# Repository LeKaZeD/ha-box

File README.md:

# HA Box

**HA Box** is an open-source, modular home automation hub built around a Raspberry Pi 5 and Home Assistant OS. It integrates the main smart home protocols (Zigbee, Thread, 433 MHz) into a single 3D-printed enclosure, with a custom ESP32 interface board providing a local E-Paper display, touch, environmental sensing, and physical controls.

---

## Project overview

HA Box is composed of four independent layers that work together:

```
+---------------------------------------------------------------+
|  3D-printed enclosure  (modular, FDM-printable, upgradeable)  |
|                                                               |
|  +---------------------------+   +-------------------------+  |
|  |  Raspberry Pi 5 stack     |   |  haboxesp PCB + ESP32   |  |
|  |  - Pi 5                   |   |  - E-Paper display      |  |
|  |  - M.2 SSD hat            |   |  - Touch (FT6336U)      |  |
|  |  - HDMI/USB-C extension   |   |  - BME280 sensor        |  |
|  |  - Sonoff Dongle Plus E   |   |  - Temp sensor TMP102   |  |
|  |    (Zigbee + Thread)      |   |  - Fan (PWM)            |  |
|  |  - CC1101 module (planned)|   |  - Buzzer               |  |
|  |    (433 MHz, SPI)         |   |  - Power button + J2    |  |
|  |                           |   |                         |  |
|  |  [ Home Assistant OS ]    |   |                         |  |
|  |  [ HA Box App (py) ]   <--+---+--> UART                 |  |
|  +---------------------------+   +-------------------------+  |
+---------------------------------------------------------------+
```

| Layer | Description | Location |
|-------|-------------|----------|
| **Hardware** | Pi 5 stack, haboxesp PCB, Sonoff dongle, connectors | `hardware/` |
| **3D enclosure** | Modular, printable enclosure for all components | `hardware/3D plan/` |
| **ESP32 firmware** | Drives display, sensors, touch, fan, buzzer | `ha-box-esp/` |
| **HA App** | Python app: UART bridge to HA API and Supervisor | `ha-box/` |
| **HA integration** | Custom component: groups all HA Box entities in the device registry | `ha-integration/` |

---

## Hardware

### Raspberry Pi 5 stack

| Component | Description | Protocol |
|-----------|-------------|----------|
| Raspberry Pi 5 | Main compute unit, runs Home Assistant OS | — |
| M.2 SSD hat | NVMe storage via PCIe | PCIe |
| HDMI + USB-C extension | Rear panel port routing | — |
| Sonoff Zigbee 3.0 USB Dongle Plus E | Zigbee and Thread coordinator | USB |
| CC1101 module | 433 MHz radio (planned) | SPI |

### haboxesp PCB + ESP32

The haboxesp is a custom PCB designed for this project. It hosts an ESP32 module and provides connectors for all user-facing peripherals. The ESP32 communicates with the Pi exclusively over UART.

| Component | Model | Interface |
|-----------|-------|-----------|
| E-Paper display | GDEY037T03-FT21 (3.7", 240×416) | SPI |
| Touch controller | FT6336U (integrated in display) | I2C |
| Environmental sensor | BME280 (temperature, humidity, pressure) | I2C |
| Case temperature | Additional sensor | I2C / analog |
| Fan | 5V PWM | PWM |
| Buzzer | Haptic feedback | GPIO |
| Power button | Wake + shutdown trigger | GPIO |
| J2 connector | Raspberry Pi J2 header (power control) | — |

PCB design files (KiCad) and manufacturing exports are in `hardware/haboxesp/`.

### 3D-printed enclosure

The enclosure is designed in Fusion 360, modular and FDM-printable. Each part can be reprinted independently to accommodate hardware upgrades.

Printable parts (STL): `Box`, `Top`, `Backplate`, `Support`, `Pied`, `Button`.

| | |
|---|---|
|  |  |

Fusion 360 source and STEP files: `hardware/3D plan/Fusion/`.

---

## ESP32 firmware

The ESP32 firmware (`ha-box-esp-fw/`) is a C++ application that:

- drives the E-Paper display (SPI) and front-light
- reads touch input (I2C, FT6336U)
- reads temperature/humidity/pressure (I2C, BME280)
- controls the fan (PWM, temperature-based)
- manages the power button (wake from deep sleep, shutdown request)
- controls the buzzer for haptic feedback
- communicates with the Pi App over UART using a line-based ASCII protocol

See [ha-box-esp-fw/ESPHOMEASSISTANT/ARCHITECTURE.md](ha-box-esp-fw/ESPHOMEASSISTANT/ARCHITECTURE.md) and [docs/ESP32_RASP_COM.md](docs/ESP32_RASP_COM.md) for the firmware architecture and UART protocol.

---

## HA App

The HA Box App (`ha-box/`) is a Home Assistant OS Supervisor App written in Python. It runs inside a Docker container on the Pi and acts as a bridge between the ESP32 (UART) and Home Assistant (HTTP API + Supervisor API).

It does not access display, sensors, or actuators directly. All peripherals are on the ESP32 side; the App communicates over UART0 and controls two Pi GPIOs (IO0 + EN) for OTA firmware updates.

### Raspberry Pi configuration (UART)

Edit `/mnt/boot/config.txt` physically (keyboard + screen on the Pi, or SD card / NVMe mounted on a computer). See [docs/HARDWARE.md](docs/HARDWARE.md#pi-configtxt-haos) for Pi 4 vs Pi 5 differences and SPI (CC1101) setup. Reboot after: `ha host reboot`.

### Installation

1. Add this repository to your Home Assistant Apps:

   Or manually: **Settings** → **App** → **App Store** → **⋮** → **Repositories** → add the URL.

2. Install **HA Box**.
3. Install the **HA Box custom integration**: copy `ha-integration/custom_components/ha_box/` to your HA `config/custom_components/` folder, then restart Home Assistant. This creates the HA Box device in the device registry.
4. Configure options according to your hardware (see below).
5. Start the App.

### Configuration

Configure options in the App UI or directly in YAML. Restart the App to apply changes.

```yaml
general:
  log_level: "info"                         # debug | info | warning | error | critical
  lang: "auto"                              # auto | fr | en

weather:
  weather_entity: "weather.forecast_home"   # HA weather entity
  update_interval: 300                      # seconds (10–3600)

bme280:
  enabled: true
  address: "auto"                           # auto | 0x76 | 0x77
  update_interval: 30                       # seconds

fan:
  enabled: false
  min_temp: 28                              # °C — fan starts
  max_temp: 60                              # °C — fan at full speed

ota:
  io0_gpio: 23                              # Pi BCM GPIO → ESP32 IO0
  en_gpio: 24                               # Pi BCM GPIO → ESP32 EN

daynight:
  update_interval: 60                       # seconds between sun.sun polls (10–3600)

clock:
  update_interval: 60                       # seconds (10–3600)

status:
  update_interval: 30                       # seconds
  exposed_addon_slugs: []                   # slugs that activate the "exposed" icon

uart:
  device: "auto"                            # auto | /dev/serial0 | /dev/ttyAMA0 | /dev/ttyUSB0

connection:
  connected_timeout: 120                    # seconds before switching to reconnecting
  reconnecting_timeout: 60                  # seconds before switching to disconnected
```

Language is auto-detected from the Home Assistant Core configuration (`/api/config` → `language`), with fallback to the container environment (`LANG`) and then English.

Fan and OTA options are sent to the ESP32 on every App startup and persisted in NVS — restart the App to apply changes.

---

## Current status (v0.2.0)

| Feature | Interface | Status |
|---------|-----------|--------|
| E-Paper display (Home, Loading, Settings pages) | SPI (ESP32) | Implemented |
| Touch navigation | I2C (ESP32) | Implemented |
| BME280 (temp, humidity, pressure) → HA entities | UART (ESP32 → Pi) | Implemented |
| TMP102 case temperature → HA entity | UART (ESP32 → Pi) | Implemented |
| Fan control (PWM, temperature-based, configurable) | PWM (ESP32) | Implemented |
| Power button (wake, soft shutdown, hard J2 stop) | UART + J2 (ESP32 ↔ Pi) | Implemented |
| Weather + clock display | UART (Pi → ESP32) | Implemented |
| HA status icons (Core, Supervisor, Net, Zigbee, Thread, Matter, External) | UART (Pi → ESP32) | Implemented |
| OTA firmware update (auto version check + flash over UART0) | UART0 + GPIO | Implemented |
| Boot failure recovery (blind OTA flash on ROM boot errors) | UART0 + GPIO | Implemented |
| Day/Night mode sync (sun.sun + manual override, HA event + binary sensor) | UART (Pi ↔ ESP32) | Implemented |
| HA Box integration (device registry, grouped entities) | HA custom component | In progress |
| CC1101 433 MHz | SPI (Pi) | Planned |

---

## Future: Compute Module board

The long-term vision is a custom carrier board built around a Raspberry Pi Compute Module, integrating the Pi, ESP32, radio modules, and all connectors on a single PCB. This would replace the current assembly of off-the-shelf boards and the haboxesp PCB with a more compact, reliable, and user-friendly product.

Early design work is in `hardware/cm5/`.

---

## Repository structure

```
ha-box/
├── hardware/
│   ├── haboxesp/          KiCad PCB project (haboxesp V0.1)
│   ├── 3D plan/           Fusion 360 enclosure + STL parts
│   └── cm5/               Compute Module carrier board (early stage)
├── ha-box-esp/         ESP32 firmware (C++)
├── ha-box/                HA App (Python)
│   ├── rootfs/            App runtime files
│   ├── config.yaml        App manifest
│   └── translations/      UI translations (en, fr)
├── ha-integration/        HA custom integration (device registry, grouped entities)
│   └── custom_components/
│       └── ha_box/
├── docs/                  Technical documentation
└── README.md
```

---

## Documentation

| Document | Description |
|----------|-------------|
| [docs/ARCHITECTURE.md](docs/ARCHITECTURE.md) | App technical architecture |
| [docs/HARDWARE.md](docs/HARDWARE.md) | Hardware specifications (haboxesp PCB + ESP32) |
| [docs/ESP32_RASP_COM.md](docs/ESP32_RASP_COM.md) | UART protocol (Pi ↔ ESP32) |
| [docs/FEATURES_STATUS.md](docs/FEATURES_STATUS.md) | Feature status and timing reference |
| [docs/TECH_STACK.md](docs/TECH_STACK.md) | Libraries and technical stack |
| [docs/I18N.md](docs/I18N.md) | Multilingual support |
| [ROADMAP.md](ROADMAP.md) | Current status and future plans |
| [CONTRIBUTING.md](CONTRIBUTING.md) | Contribution guide |
| [ha-box/SECURITY.md](ha-box/SECURITY.md) | Security policy |
| [TESTING.md](TESTING.md) | Development and testing guide |

---

## Contributing

Contributions are welcome. See [CONTRIBUTING.md](CONTRIBUTING.md) to get started.

---

## License

Apache License 2.0. See [LICENSE](LICENSE).

---

*Project started January 17, 2026*

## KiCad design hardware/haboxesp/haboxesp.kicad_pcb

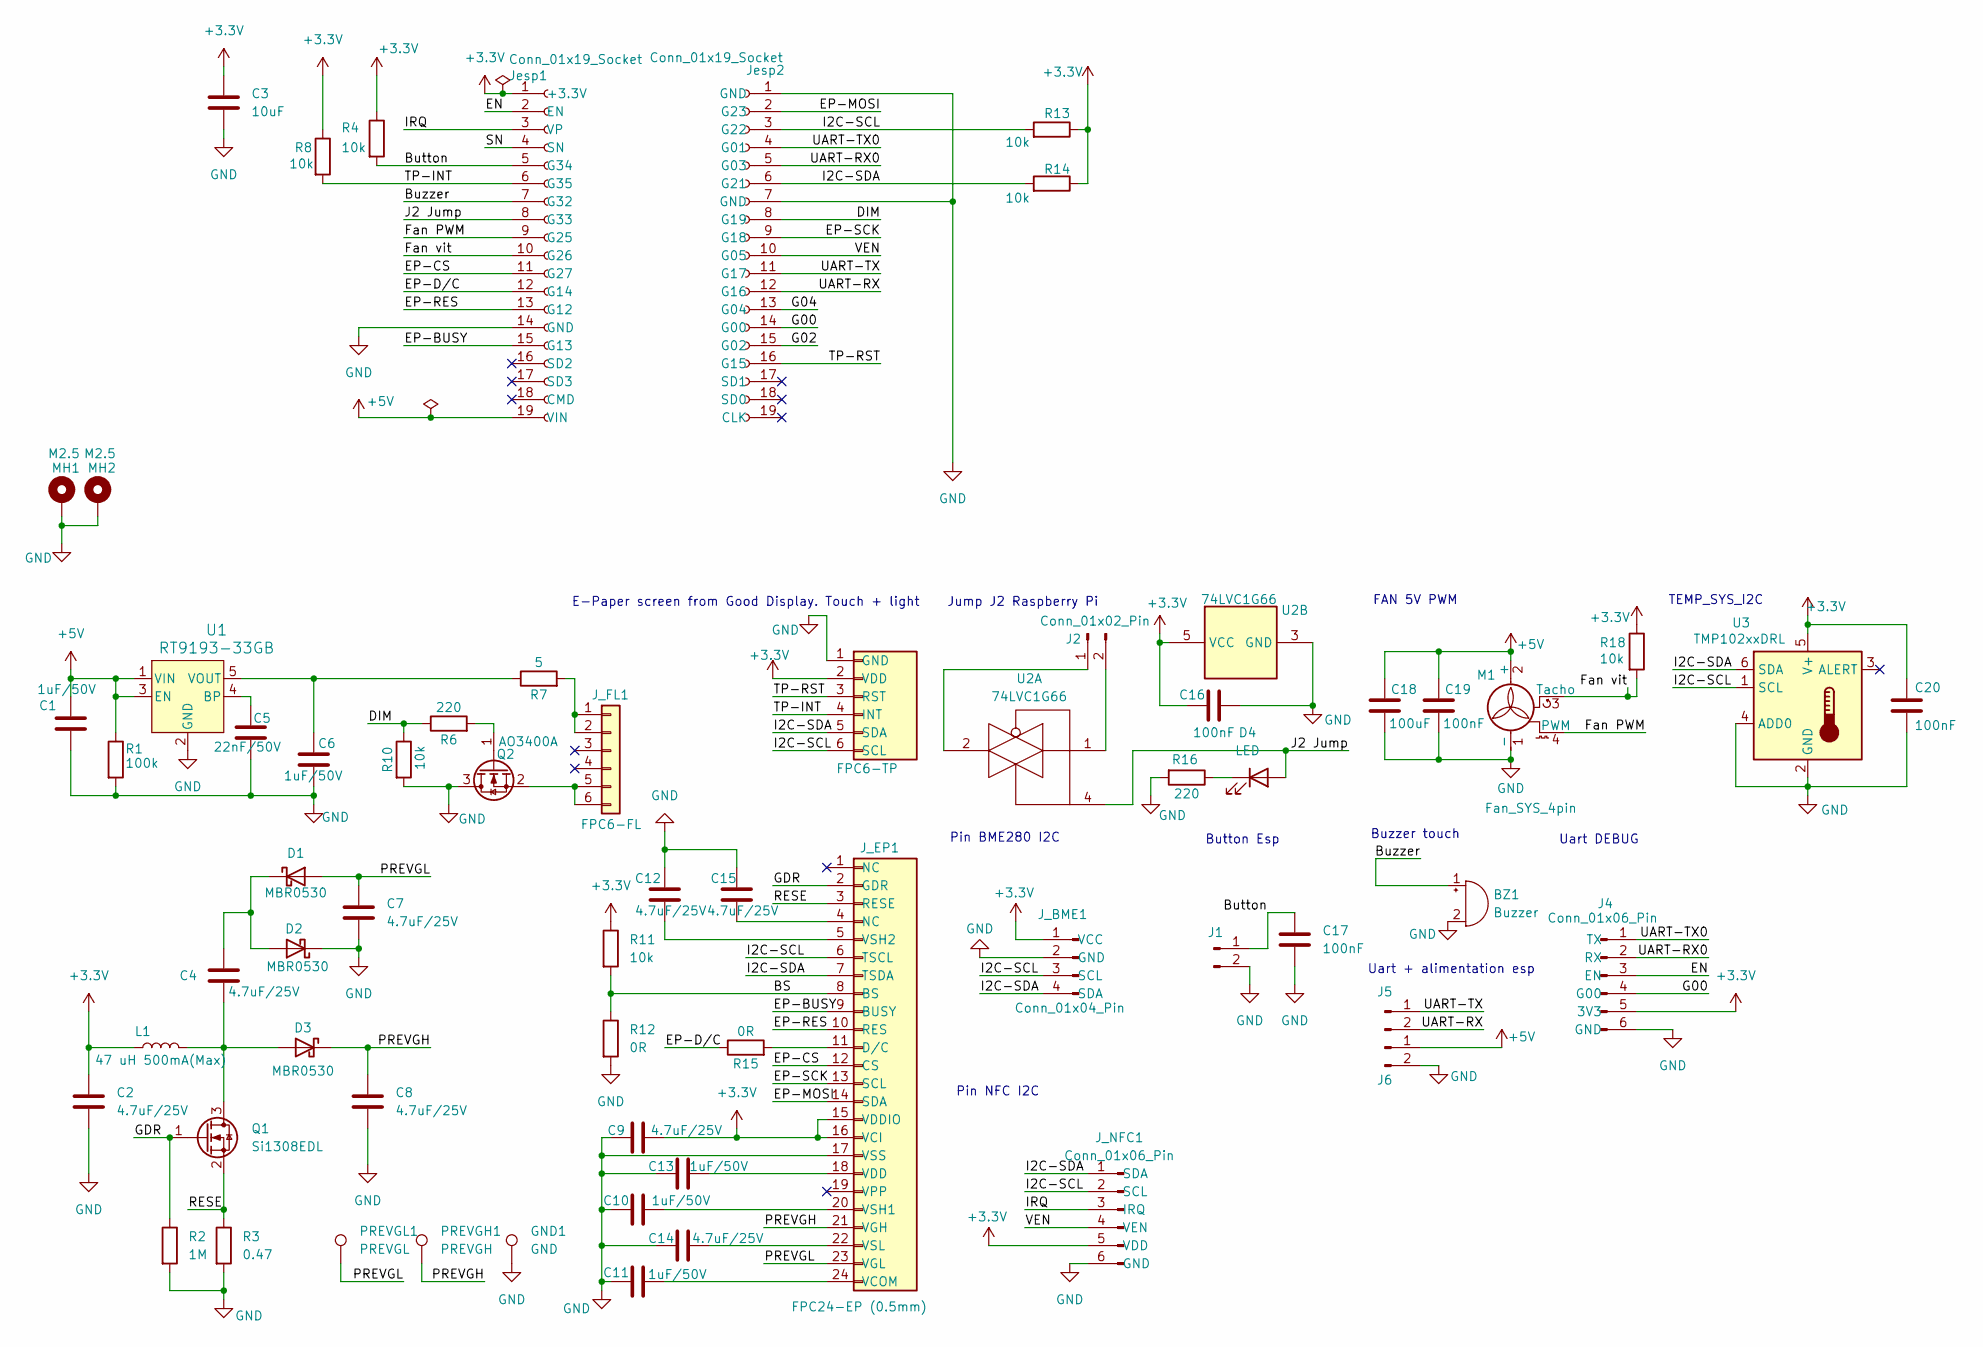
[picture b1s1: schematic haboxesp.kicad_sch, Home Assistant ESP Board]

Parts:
BZ1: Buzzer; Buzzer_12x9.5RM7.6; MFR.Part HYT-1205 IC; LCSC C7544833
C1, C6, C10, C11, C13: 1uF/50V; C_0603_1608Metric; MFR.Part CL10A105KB8NNNC; LCSC C15849
C2, C4, C7, C8, C9, C12, C14, C15: 4.7uF/25V; C_0603_1608Metric; MFR.Part CL10A475KA8NQNC; LCSC C69335
C3: 10uF; C_0603_1608Metric; MFR.Part CL10A106KP8NNNC; LCSC C19702
C5: 22nF/50V; C_0603_1608Metric; MFR.Part CL10B223KB8NNNC; LCSC C21122
C16, C17, C19, C20: 100nF; C_0603_1608Metric; MFR.Part CC0603KRX7R9BB104; LCSC C14663
C18: 100uF; CP_Elec_6.3x5.4; MFR.Part FVH016ADA101M0654; LCSC C7469977
D1, D2, D3: MBR0530; D_SOD-123; MFR.Part MBR0530; LCSC C77336
D4: LED; LED_0603_1608Metric; MFR.Part KT-0603R; LCSC C2286
GND1: GND; TestPoint_Pad_D2.0mm
J1, J2, J5, J6: Conn_01x02_Pin; PinHeader_1x02_P2.54mm_Vertical
J4: Conn_01x06_Pin; PinHeader_1x06_P2.54mm_Vertical
J_BME1: Conn_01x04_Pin; PinHeader_1x04_P2.54mm_Vertical
J_EP1: FPC24-EP (0.5mm); Hirose_FH12-24S-0.5SH_1x24-1MP_P0.50mm_Horizontal; MFR.Part KH-FPC0.5-H2.0SMT-24P-QCHF; LCSC C3249999
J_FL1: FPC6-FL; Hirose_FH12-6S-0.5SH_1x06-1MP_P0.50mm_Horizontal; MFR.Part KH-FPC0.5-H2.0SMT-6P-QCHF; LCSC C3249990
J_NFC1: Conn_01x06_Pin; PinHeader_1x06_P2.54mm_Vertical
J_TP1: FPC6-TP; Hirose_FH12-6S-0.5SH_1x06-1MP_P0.50mm_Horizontal; MFR.Part KH-FPC0.5-H2.0SMT-6P-QCHF; LCSC C3249990
Jesp1, Jesp2: Conn_01x19_Socket; PinSocket_1x19_P2.54mm_Vertical
L1: 47 uH 500mA(Max); L_1812_4532Metric; MFR.Part ACC4532470K2B; LCSC C22469103
M1: Fan_SYS_4pin; FanPinHeader_1x04_P2.54mm_Vertical
MH1, MH2: M2.5; MountingHole_2.7mm_M2.5_Pad_Via
PREVGH1: PREVGH; TestPoint_Pad_D2.0mm
PREVGL1: PREVGL; TestPoint_Pad_D2.0mm
Q1: Si1308EDL; SOT-323_SC-70; MFR.Part SI1308EDL-VB; LCSC C4355112
Q2: AO3400A; SOT-23; MFR.Part AO3400A; LCSC C20917
R1: 100k; R_0603_1608Metric; MFR.Part 0603WAF1003T5E; LCSC C25803
R2: 1M; R_0603_1608Metric; MFR.Part 0603WAF1004T5E; LCSC C22935
R3: 0.47; R_0603_1608Metric; MFR.Part 0603WAF470LT5E; LCSC C23411
R4, R8, R10, R11, R13, R14, R18: 10k; R_0603_1608Metric; MFR.Part 0603WAF1002T5E; LCSC C25804
R6, R16: 220; R_0603_1608Metric; MFR.Part 0603WAF2200T5E; LCSC C22962
R7: 5; R_0603_1608Metric; MFR.Part 0603WAF510KT5E; LCSC C25197
R12, R15: 0R; R_0603_1608Metric; MFR.Part 0603WAF0000T5E; LCSC C21189
U1: RT9193-33GB; SOT-23-5_RIT; MFR.Part RT9193-33GB; LCSC C15651
U2: 74LVC1G66; SOT-353_SC-70-5; MFR.Part U74LVC1G66G; LCSC C7509611
U3: TMP102xxDRL; SOT-563; MFR.Part TMP102AIDRLR; LCSC C99269

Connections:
+3.3V: C2.1, C3.1, C9.2, C16.1, C20.1, J4.5 (3V3), J_BME1.1 (VCC), J_EP1.15 (VDDIO), J_EP1.16 (VCI), J_NFC1.5 (VDD), J_TP1.2 (VDD), Jesp1.1 (+3.3V), L1.1, R4.1, R8.1, R11.1, R13.1, R14.1, R18.1, U2.5 (VCC), U3.5 (V+)
+5V: C1.1, C18.1, C19.1, J6.1, Jesp1.19 (VIN), M1.2 (+), R1.1, U1.1 (VIN), U1.3 (EN)
/BS: J_EP1.8 (BS), R11.2, R12.1
/Button: C17.1, J1.1, Jesp1.5 (G34), R4.2
/Buzzer: BZ1.1 (+), Jesp1.7 (G32)
/DIM: Jesp2.8 (G19), R6.1, R10.1
/EN: J4.3 (EN), Jesp1.2 (EN)
/EP-BUSY: J_EP1.9 (BUSY), Jesp1.15 (G13)
/EP-CS: J_EP1.12 (CS), Jesp1.11 (G27)
/EP-D/C: Jesp1.12 (G14), R15.1
/EP-MOSI: J_EP1.14 (SDA), Jesp2.2 (G23)
/EP-RES: J_EP1.10 (RES), Jesp1.13 (G12)
/EP-SCK: J_EP1.13 (SCL), Jesp2.9 (G18)
/Fan PWM: Jesp1.9 (G25), M1.4 (PWM)
/Fan vit: Jesp1.10 (G26), M1.3 (Tacho), R18.2
/G00: J4.4 (G00), Jesp2.14 (G00)
/G02: Jesp2.15 (G02)
/G04: Jesp2.13 (G04)
/GDR: J_EP1.2 (GDR), Q1.1 (G), R2.1
/I2C-SCL: J_BME1.3 (SCL), J_EP1.6 (TSCL), J_NFC1.2 (SCL), J_TP1.6 (SCL), Jesp2.3 (G22), R13.2, U3.1 (SCL)
/I2C-SDA: J_BME1.4 (SDA), J_EP1.7 (TSDA), J_NFC1.1 (SDA), J_TP1.5 (SDA), Jesp2.6 (G21), R14.2, U3.6 (SDA)
/IRQ: J_NFC1.3 (IRQ), Jesp1.3 (VP)
/J2 Jump: D4.2 (A), Jesp1.8 (G33), U2.4
/PREVGH: C8.1, D3.1 (K), J_EP1.21 (VGH), PREVGH1.1
/PREVGL: C7.1, D1.2 (A), J_EP1.23 (VGL), PREVGL1.1
/RESE: J_EP1.3 (RESE), Q1.2 (S), R3.1
/SN: Jesp1.4 (SN)
/TP-INT: J_TP1.4 (INT), Jesp1.6 (G35), R8.2
/TP-RST: J_TP1.3 (RST), Jesp2.16 (G15)
/UART-RX: J5.2, Jesp2.12 (G16)
/UART-RX0: J4.2 (RX), Jesp2.5 (G03)
/UART-TX: J5.1, Jesp2.11 (G17)
/UART-TX0: J4.1 (TX), Jesp2.4 (G01)
/VEN: J_NFC1.4 (VEN), Jesp2.10 (G05)
GND: BZ1.2 (-), C1.2, C2.2, C3.2, C5.2, C6.2, C7.2, C8.2, C9.1, C10.1, C11.1, C12.1, C13.1, C14.2, C15.1, C16.2, C17.2, C18.2, C19.2, C20.2, D2.1 (K), GND1.1, J1.2, J4.6 (GND), J6.2, J_BME1.2 (GND), J_EP1.17 (VSS), J_NFC1.6 (GND), J_TP1.1 (GND), Jesp1.14 (GND), Jesp2.1 (GND), Jesp2.7 (GND), M1.1 (-), MH1.1, MH2.1, Q2.3 (D), R1.2, R2.2, R3.2, R10.2, R12.2, R16.2, U1.2 (GND), U2.3 (GND), U3.2 (GND), U3.4 (ADD0)
unnamed: C15.2, J_EP1.4 (NC)
unnamed: C4.1, D1.1 (K), D2.2 (A)
unnamed: C4.2, D3.2 (A), L1.2, Q1.3 (D)
unnamed: D4.1 (K), R16.1
unnamed: J2.1, U2.2
unnamed: J2.2, U2.1
unnamed: J_EP1.11 (D/C), R15.2
unnamed: C11.2, J_EP1.24 (VCOM)
unnamed: C13.2, J_EP1.18 (VDD)
unnamed: C10.2, J_EP1.20 (VSH1)
unnamed: C12.2, J_EP1.5 (VSH2)
unnamed: C14.1, J_EP1.22 (VSL)
unnamed: J_FL1.1, J_FL1.2, R7.2
unnamed: J_FL1.5, J_FL1.6, Q2.2 (S)
unnamed: Q2.1 (G), R6.2
unnamed: C5.1, U1.4 (BP)
unnamed: C6.1, R7.1, U1.5 (VOUT)

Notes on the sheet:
FAN 5V PWM
TEMP_SYS_I2C
Pin BME280 I2C
E-Paper screen from Good Display. Touch + light
Uart + alimentation esp
Uart DEBUG
Jump J2 Raspberry Pi
Button Esp
Pin NFC I2C
Buzzer touch

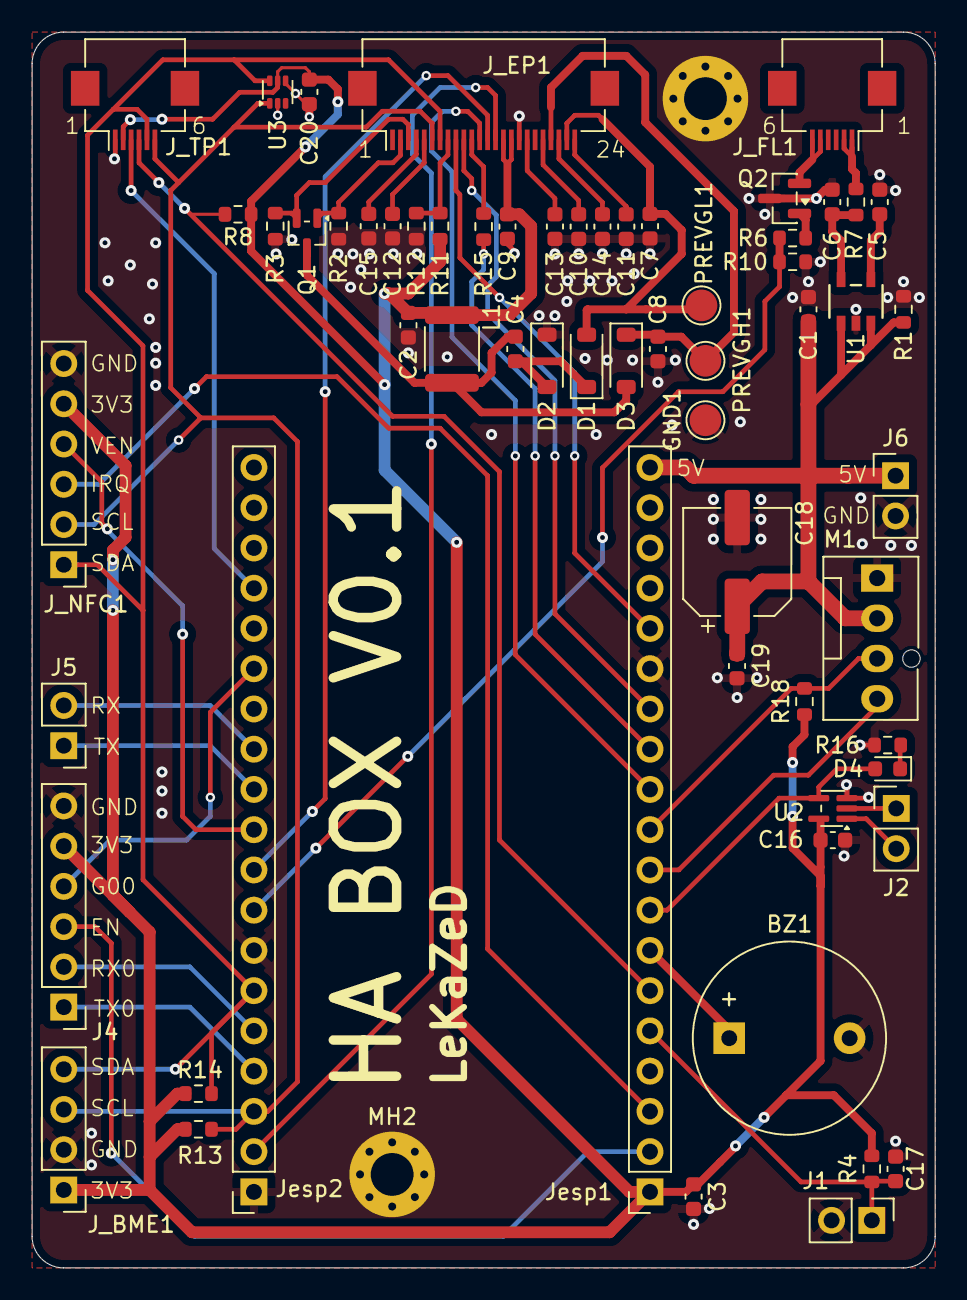
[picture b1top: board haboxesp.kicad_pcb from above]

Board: 2 copper layers, 57.0 x 78.0 mm, 64 parts (0 on the bottom side), 49 nets.

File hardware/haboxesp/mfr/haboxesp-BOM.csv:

"Designator","Quantity","Value","Manufacturer","MFR.Part","LCSC"
"D4","1","LED","LED_SMD:LED_0603_1608Metric","Hubei KENTO Elec","KT-0603R","C2286"
"C16,C17,C19,C20","4","100nF","Capacitor_SMD:C_0603_1608Metric","YAGEO","CC0603KRX7R9BB104","C14663"
"U1","1","RT9193-33GB","RT9193-33GB:SOT-23-5_RIT","RICHTEK","RT9193-33GB","C15651"
"C1,C6,C10,C11,C13","5","1uF/50V","Capacitor_SMD:C_0603_1608Metric","Samsung Electro-Mechanics","CL10A105KB8NNNC","C15849"
"C3","1","10uF","Capacitor_SMD:C_0603_1608Metric","Samsung Electro-Mechanics","CL10A106KP8NNNC","C19702"
"Q2","1","AO3400A","Package_TO_SOT_SMD:SOT-23","Alpha & Omega Semicon","AO3400A","C20917"
"C5","1","22nF/50V","Capacitor_SMD:C_0603_1608Metric","Samsung Electro-Mechanics","CL10B223KB8NNNC","C21122"
"R12,R15","2","0R","Resistor_SMD:R_0603_1608Metric","UNI-ROYAL(Uniroyal Elec)","0603WAF0000T5E","C21189"
"R2","1","1M","Resistor_SMD:R_0603_1608Metric","UNI-ROYAL(Uniroyal Elec)","0603WAF1004T5E","C22935"
"R6,R16","2","220","Resistor_SMD:R_0603_1608Metric","UNI-ROYAL(Uniroyal Elec)","0603WAF2200T5E","C22962"
"R3","1","0.47","Resistor_SMD:R_0603_1608Metric","UNI-ROYAL(Uniroyal Elec)","0603WAF470LT5E","C23411"
"R7","1","5","Resistor_SMD:R_0603_1608Metric","UNI-ROYAL(Uniroyal Elec)","0603WAF510KT5E","C25197"
"R1","1","100k","Resistor_SMD:R_0603_1608Metric","UNI-ROYAL(Uniroyal Elec)","0603WAF1003T5E","C25803"
"R4,R8,R10,R11,R13,R14,R18","7","10k","Resistor_SMD:R_0603_1608Metric","UNI-ROYAL(Uniroyal Elec)","0603WAF1002T5E","C25804"
"C2,C4,C7,C8,C9,C12,C14,C15","8","4.7uF/25V","Capacitor_SMD:C_0603_1608Metric","Samsung Electro-Mechanics","CL10A475KA8NQNC","C69335"
"D1,D2,D3","3","MBR0530","Diode_SMD:D_SOD-123","Jiangsu Changjing Electronics Technology Co., Ltd.","MBR0530","C77336"
"U3","1","TMP102xxDRL","Package_TO_SOT_SMD:SOT-563","Texas Instruments","TMP102AIDRLR","C99269"
"J_FL1","1","FPC6-FL","Connector_FFC-FPC:Hirose_FH12-6S-0.5SH_1x06-1MP_P0.50mm_Horizontal","Shenzhen Kinghelm Elec","KH-FPC0.5-H2.0SMT-6P-QCHF","C3249990"
"J_TP1","1","FPC6-TP","Connector_FFC-FPC:Hirose_FH12-6S-0.5SH_1x06-1MP_P0.50mm_Horizontal","Shenzhen Kinghelm Elec","KH-FPC0.5-H2.0SMT-6P-QCHF","C3249990"
"J_EP1","1","FPC24-EP (0.5mm)","Connector_FFC-FPC:Hirose_FH12-24S-0.5SH_1x24-1MP_P0.50mm_Horizontal","Shenzhen Kinghelm Elec","KH-FPC0.5-H2.0SMT-24P-QCHF","C3249999"
"Q1","1","Si1308EDL","Package_TO_SOT_SMD:SOT-323_SC-70","VBsemi Elec","SI1308EDL-VB","C4355112"
"C18","1","100uF","Capacitor_SMD:CP_Elec_6.3x5.4","FOSAN","FVH016ADA101M0654","C7469977"
"U2","1","74LVC1G66","Package_TO_SOT_SMD:SOT-353_SC-70-5","UTC(Unisonic Tech)","U74LVC1G66G","C7509611"
"BZ1","1","Buzzer","Buzzer_Beeper:Buzzer_12x9.5RM7.6","HYDZ","HYT-1205 IC","C7544833"
"L1","1","47 uH 500mA(Max)","Inductor_SMD:L_1812_4532Metric","ABC","ACC4532470K2B","C22469103"

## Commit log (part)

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2026-01-17 first commit, welcome on homebox
2026-01-18 phase 2
2026-01-19 added hardware selection & 3d design
2026-01-19 Added multilingual support documentation and updated roadmap for Phase 2.1, including tasks for translation implementation and integration. Removed example files and added I18N.md for detailed multil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
2026-01-20 Refactor documentation to English, update project descriptions, and enhance configuration options. Added testing guide and improved error handling in API client. Updated README, CONTRIBUTING, and var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
2026-01-20 Update .gitignore to include development files for amd64 setup, enhance README with security and testing documentation, and revise ROADMAP to reflect project status. Add SECURITY.md for comprehensive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
2026-01-20 Implement multilingual support by completing translation infrastructure and adding English and French translation files. Update ROADMAP and I18N documentation to reflect the completed status of Phase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
2026-01-26 Bump actions/checkout from 6.0.1 to 6.0.2
    Bumps [actions/checkout](https://github.com/actions/checkout) from 6.0.1 to 6.0.2.
    - [Release notes](https://github.com/actions/checkout/releases)
    - [Changelog](https://github.com/actions/checkout/blob/main/CHANGELOG.md)
    - [Commits](https://github.com/actions/checkout/compare/v6.0.1...v6.0.2)
    ---
    updated-dependencies:
2026-02-02 Bump docker/login-action from 3.6.0 to 3.7.0
    Bumps [docker/login-action](https://github.com/docker/login-action) from 3.6.0 to 3.7.0.
    - [Release notes](https://github.com/docker/login-action/releases)
    - [Commits](https://github.com/docker/login-action/compare/v3.6.0...v3.7.0)
    ---
    updated-dependencies:
    - dependency-name: docker/login-action
2026-02-19 Add AsciiProto, BME280, FanController, PowerButton, and i18n modules for enhanced hardware interaction and multilingual support. Implemented configuration options for buzzer and display, and establis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
2026-02-20 Refactor comments and variable names in ESPHOMEASSISTANT codebase for improved clarity and consistency. Updated language-related identifiers and documentation comments to enhance readability. Removed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
2026-02-23 Refactor ESPHOMEASSISTANT code to improve UI management and language handling. Consolidated UI-related configurations and callbacks into a new ui_entry.h file for better organization. Updated languag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
2026-02-23 Enhance compliance with Home Assistant Apps documentation by adding detailed guidelines in .cursorrules. Introduce new documentation files for HA Apps compliance and architecture of ESP32 communicati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
2026-02-23 Update documentation to reflect terminology changes from "add-on" to "App" throughout various files, including .cursorrules, README, CONTRIBUTING, and others. Adjust references in configuration and s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
2026-03-05 Update version to 0.1.38 and add StatusHandler for system status updates. Introduce new status fetchers for Core, Supervisor, network, and various integrations (Zigbee, Thread, Matter, etc.). Enhance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
2026-03-05 Remove EpdUc8253 class implementation and header files from ESPHOMEASSISTANT. Update model to include new connectivity status flags for core, supervisor, network, LAN, WiFi, and external access. Intr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
2026-03-05 Bump home-assistant/builder from 2025.11.0 to 2026.02.1
    Bumps [home-assistant/builder](https://github.com/home-assistant/builder) from 2025.11.0 to 2026.02.1.
    - [Release notes](https://github.com/home-assistant/builder/releases)
    - [Commits](https://github.com/home-assistant/builder/compare/2025.11.0...2026.02.1)
    ---
    updated-dependencies:
    - dependency-name: home-assistant/builder
2026-03-05 Update copyright year in LICENSE file to 2026 and specify the copyright owner as Alexandre Konzelmann.
2026-03-05 Update config.yaml to comment out boot and apparmor options, and gpio and kernel_modules settings for improved configurability.
2026-03-05 Update documentation and configuration for NFC integration and hardware specifications
    - Changed references from PN532 to PN7161 for the NFC reader in various documentation files, including README.md, HARDWARE.md, and translations.
    - Updated the communication and features documentation to reflect the new NFC module and its configuration.
    - Added a new document detailing the status communication between Home Assistant and the ESP32.
    - Adjusted the requirements.txt to specify the PN7161 library for future NFC integration.
    - Enhanced the architecture documentation to clarify the ESP32's role in handling NFC communications.
    Files modified:
2026-03-09 Bump docker/login-action from 3.7.0 to 4.0.0
    Bumps [docker/login-action](https://github.com/docker/login-action) from 3.7.0 to 4.0.0.
    - [Release notes](https://github.com/docker/login-action/releases)
    - [Commits](https://github.com/docker/login-action/compare/v3.7.0...v4.0.0)
    ---
    updated-dependencies:
    - dependency-name: docker/login-action
2026-03-16 Update README.md and add hardware files for HA Box project
    - Expanded the README.md to include a hardware overview section detailing the custom enclosure and PCB design.
    - Added new 3D model files for the HA Box components, including STL and STEP files for various parts.
    - Included images of the HA Box enclosure and PCB to enhance documentation.
    Files modified:
    - README.md
    - hardware/3D plan/Box parts/Backplate.stl
2026-03-23 Bump home-assistant/builder from 2026.02.1 to 2026.03.2
    Bumps [home-assistant/builder](https://github.com/home-assistant/builder) from 2026.02.1 to 2026.03.2.
    - [Release notes](https://github.com/home-assistant/builder/releases)
    - [Commits](https://github.com/home-assistant/builder/compare/2026.02.1...2026.03.2)
    ---
    updated-dependencies:
    - dependency-name: home-assistant/builder
2026-03-27 Add new STEP files for HA Box components and update STL files
    - Introduced new STEP files for various components of the HA Box, including Backplate, Box, Button, Foot, and Support.
    - Updated existing STL files for the Box and Button components to reflect the latest designs.
    - Removed the obsolete Box.gcode file and the Pied.stl file.
    Files modified:
    - hardware/3D plan/Box parts/Backplate.step
    - hardware/3D plan/Box parts/Box.step
2026-03-29 Enhance documentation and add new features for HA Box project
    - Updated README.md to provide a comprehensive project overview, including hardware layers and detailed descriptions of components.
    - Added a Bill of Materials (BOM) document listing all components required for building the HA Box V0.1, including pricing and links.
    - Introduced new features in the ESP32 firmware, including support for the TMP102 temperature sensor and front-light control.
    - Enhanced the user interface with a new shutdown page and corresponding language support for shutdown messages.
    Files modified:
    - README.md
2026-03-31 Update ESP32 firmware documentation and enhance fan control features
    - Revised the ESP32_RASP_COM.md to include detailed descriptions of the new case temperature sensor (TMP102) and fan PWM control features.
    - Added a new README.md for the ESP32 firmware, outlining prerequisites, build instructions, and OTA update plans.
    - Implemented fan configuration persistence in the firmware, allowing runtime adjustments via the Pi.
    - Introduced new icons for the user interface, including power plug icons for enhanced visual feedback.
    Files modified:
    - docs/ESP32_RASP_COM.md
2026-03-31 Enhance documentation and add features for HA Box
    - Updated .cursorrules to clarify changelog requirements for significant changes in the HA Box add-on.
    - Introduced a new FEATURES_STATUS.md file to track the status of features for the HA Box, organized by responsibility and including details for both ESP32 and Pi components.
    - Updated config.yaml to reflect the new version 0.1.45 and adjusted the ESP32 configuration section for clarity.
    - Revised README.md to include updated instructions for the Raspberry Pi configuration.
    Files modified:
    - .cursorrules
2026-03-31 Add TODO file to .gitignore
2026-04-06 Bump docker/login-action from 4.0.0 to 4.1.0
    Bumps [docker/login-action](https://github.com/docker/login-action) from 4.0.0 to 4.1.0.
    - [Release notes](https://github.com/docker/login-action/releases)
    - [Commits](https://github.com/docker/login-action/compare/v4.0.0...v4.1.0)
    ---
    updated-dependencies:
    - dependency-name: docker/login-action
2026-05-20 Release v0.2.0
    Squash merge of develop into main for the v0.2.0 release.
    Key additions:
    - OTA firmware update (auto-flash, blind recovery, VERSION verb retry)
    - Shutdown detection with HALTING state and accelerated heartbeat
    - Pi alive hardware signal via GPIO5
    - CC1101 433 MHz RF module (experimental, RFLink TCP port 5557)
2026-05-21 docs: rename add-on to App (official HA terminology)
    Update all documentation references from "add-on" to "App" following
    the Home Assistant official terminology change. Remove .cursorrules
    (obsolete).
2026-05-25 Bump docker/login-action from 4.0.0 to 4.2.0
    Bumps [docker/login-action](https://github.com/docker/login-action) from 4.0.0 to 4.2.0.
    - [Release notes](https://github.com/docker/login-action/releases)
    - [Commits](https://github.com/docker/login-action/compare/v4.0.0...v4.2.0)
    ---
    updated-dependencies:
    - dependency-name: docker/login-action
2026-06-08 Bump actions/checkout from 6.0.2 to 6.0.3
    Bumps [actions/checkout](https://github.com/actions/checkout) from 6.0.2 to 6.0.3.
    - [Release notes](https://github.com/actions/checkout/releases)
    - [Changelog](https://github.com/actions/checkout/blob/main/CHANGELOG.md)
    - [Commits](https://github.com/actions/checkout/compare/v6.0.2...v6.0.3)
    ---
    updated-dependencies:
2026-06-22 Bump actions/checkout from 6.0.2 to 7.0.0
    Bumps [actions/checkout](https://github.com/actions/checkout) from 6.0.2 to 7.0.0.
    - [Release notes](https://github.com/actions/checkout/releases)
    - [Changelog](https://github.com/actions/checkout/blob/main/CHANGELOG.md)
    - [Commits](https://github.com/actions/checkout/compare/v6.0.2...v7.0.0)
    ---
    updated-dependencies:
2026-06-22 Bump home-assistant/builder from 2026.03.2 to 2026.06.0
    Bumps [home-assistant/builder](https://github.com/home-assistant/builder) from 2026.03.2 to 2026.06.0.
    - [Release notes](https://github.com/home-assistant/builder/releases)
    - [Commits](https://github.com/home-assistant/builder/compare/2026.03.2...2026.06.0)
    ---
    updated-dependencies:
    - dependency-name: home-assistant/builder

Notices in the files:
README.md:
License: Apache 2.0
